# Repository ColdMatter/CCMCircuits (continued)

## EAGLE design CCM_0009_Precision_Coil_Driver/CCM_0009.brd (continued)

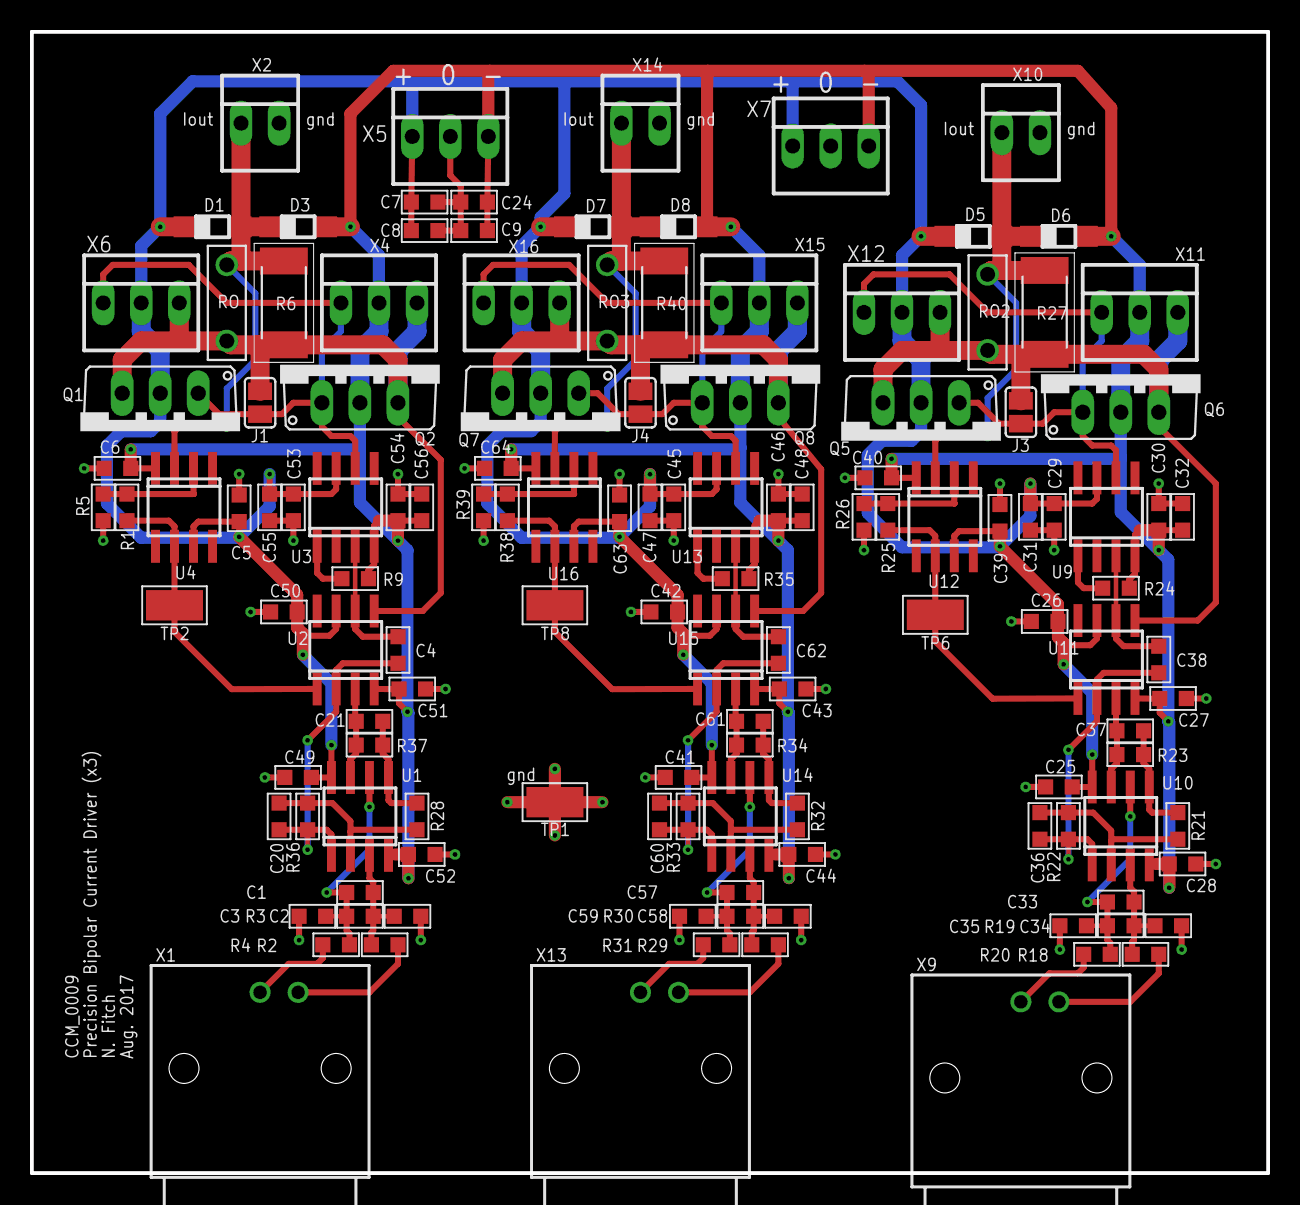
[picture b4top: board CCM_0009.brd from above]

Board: 2 copper layers, 82.5 x 76.2 mm, 130 parts (0 on the bottom side), 48 nets.

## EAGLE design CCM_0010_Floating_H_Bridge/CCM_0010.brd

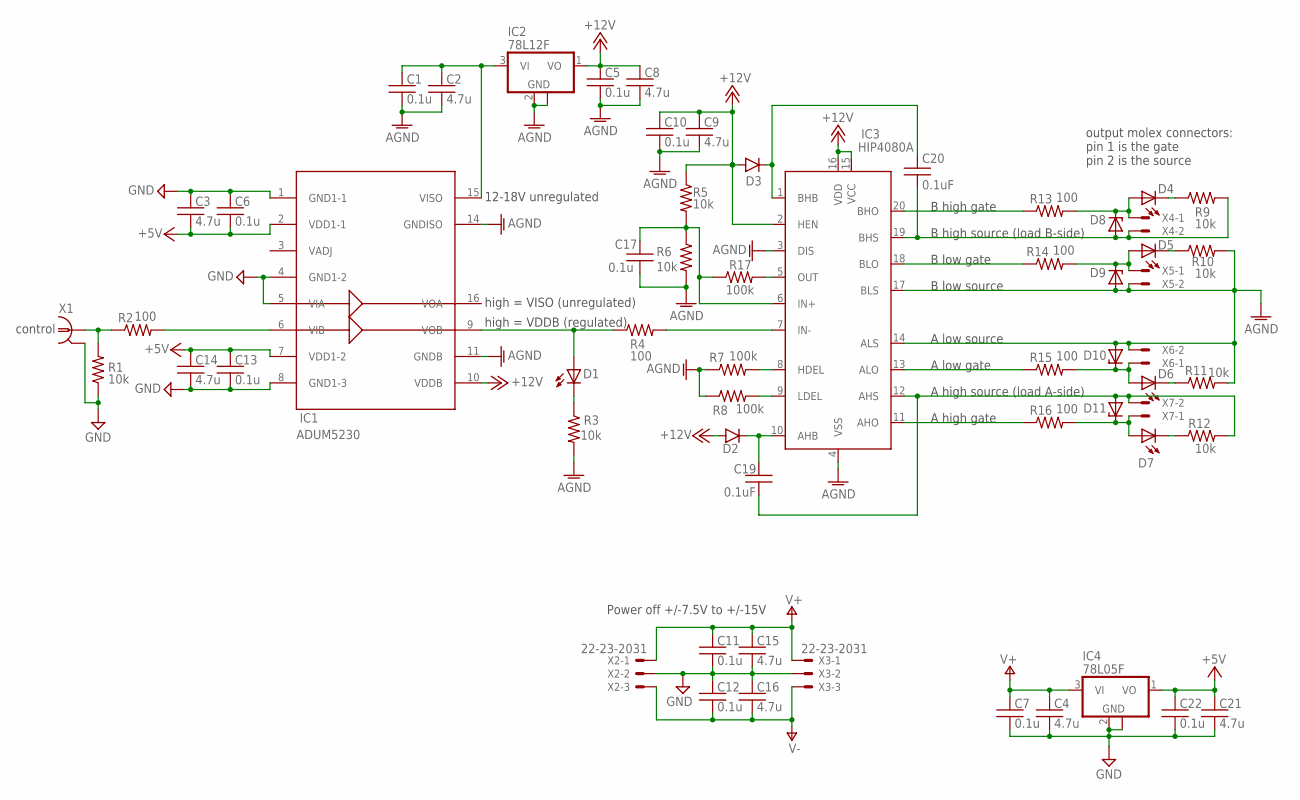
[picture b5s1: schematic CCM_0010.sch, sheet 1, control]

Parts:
C1, C5, C6, C7, C10, C11, C12, C13, C17, C22: 0.1u; 0603
C2, C3, C4, C8, C9, C14, C15, C16, C21: 4.7u; 0603
C19, C20: 0.1uF; 0603
D1, D4, D5, D6, D7: LED0603
D2, D3: DIODESOT23; SOT23-3
D8, D9, D10, D11: ZENER-DIODESOT23; SOT23
IC1: ADUM5230; SO16W
IC2: 78L12F; SOT89
IC3: HIP4080A; SO20W
IC4: 78L05F; SOT89
R1, R3, R5, R6, R9, R10, R11, R12: 10k; 0603
R2, R4, R13, R14, R15, R16: 100; 0603
R7, R8, R17: 100k; 0603
X1: 1-227161-0; AMP_227161
X2, X3: 22-23-2031
X4, X5, X6, X7: 22-23-2021

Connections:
+5V: C3.2, C6.2, C13.1, C14.1, C21.1, C22.1, IC1.2 (VDD1-1), IC1.7 (VDD1-2), IC4.1 (VO)
+12V: C5.1, C8.1, C9.1, C10.1, D2.1 (A), D3.1 (A), IC1.10 (VDDB), IC2.1 (VO), IC3.2 (HEN), IC3.15 (VCC), IC3.16 (VDD), R5.1
AGND: C1.2, C2.2, C5.2, C8.2, C9.2, C10.2, C17.2, D9.1 (A), D10.1 (A), IC1.11 (GNDB), IC1.14 (GNDISO), IC2.2 (GND), IC2.2@1 (GND), IC3.3 (DIS), IC3.4 (VSS), IC3.14 (ALS), IC3.17 (BLS), R3.2, R6.2, R7.1, R8.1, R10.2, R11.2, X5.2, X6.2
GND: C3.1, C4.2, C6.1, C7.2, C11.2, C12.1, C13.2, C14.2, C15.2, C16.1, C21.2, C22.2, IC1.1 (GND1-1), IC1.4 (GND1-2), IC1.5 (VIA), IC1.8 (GND1-3), IC4.2 (GND), IC4.2@1 (GND), R1.1, X1.2, X2.2, X3.2
unnamed: D1.C, R3.1
unnamed: D4.C, R9.1
unnamed: D5.C, R10.1
unnamed: IC3.20 (BHO), R13.1
unnamed: D5.A, D9.3 (C), R14.2, X5.1
unnamed: D6.C, R11.1
unnamed: D4.A, D8.3 (C), R13.2, X4.1
unnamed: D1.A, IC1.9 (VOB), R4.1
unnamed: D7.C, R12.1
unnamed: C1.1, C2.1, IC1.15 (VISO), IC2.3 (VI)
unnamed: IC3.11 (AHO), R16.1
unnamed: IC3.13 (ALO), R15.1
unnamed: IC3.7 (IN-), R4.2
unnamed: IC3.9 (LDEL), R8.2
unnamed: C20.2, D3.3 (C), IC3.1 (BHB)
unnamed: C20.1, D8.1 (A), IC3.19 (BHS), R9.2, X4.2
unnamed: IC3.18 (BLO), R14.1
unnamed: IC3.5 (OUT), R17.2
unnamed: C19.1, D11.1 (A), IC3.12 (AHS), R12.2, X7.2
unnamed: D7.A, D11.3 (C), R16.2, X7.1
unnamed: C19.2, D2.3 (C), IC3.10 (AHB)
unnamed: IC3.8 (HDEL), R7.2
unnamed: D6.A, D10.3 (C), R15.2, X6.1
unnamed: R1.2, R2.1, X1.1
unnamed: C17.1, IC3.6 (IN+), R5.2, R6.1, R17.1
unnamed: IC1.6 (VIB), R2.2
V+: C4.1, C7.1, C11.1, C15.1, IC4.3 (VI), X2.1, X3.1
V-: C12.2, C16.2, X2.3, X3.3

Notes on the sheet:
B high source (load B-side)
B high gate
B low gate
B low source
A high gate
A high source (load A-side)
A low gate
A low source
control
12-18V unregulated
high = VISO (unregulated)
high = VDDB (regulated)
Power off +/-7.5V to +/-15V
output molex connectors: pin 1 is the gate pin 2 is the source

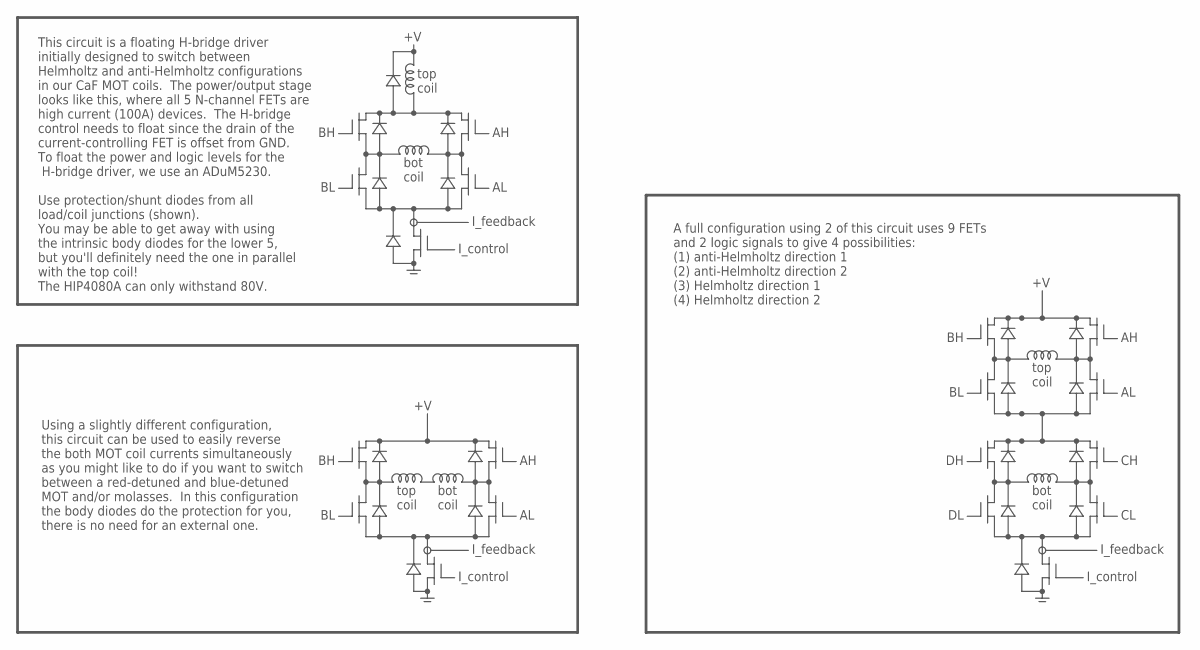
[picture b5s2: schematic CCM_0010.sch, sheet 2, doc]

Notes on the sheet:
I_control
top coil
bot coil
This circuit is a floating H-bridge driver initially designed to switch between Helmholtz and anti-Helmholtz configurations in our CaF MOT coils. The power/output stage looks like this, where all 5 N-channel FETs are high current (100A) devices. The H-bridge control needs to float since the drain o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
I_feedback
Using a slightly different configuration, this circuit can be used to easily reverse the both MOT coil currents simultaneously as you might like to do if you want to switch between a red-detuned and blue-detuned MOT and/or molasses. In this configuration the body diodes do the protection for you, t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
A full configuration using 2 of this circuit uses 9 FETs and 2 logic signals to give 4 possibilities: (1) anti-Helmholtz direction 1 (2) anti-Helmholtz direction 2 (3) Helmholtz direction 1 (4) Helmholtz direction 2

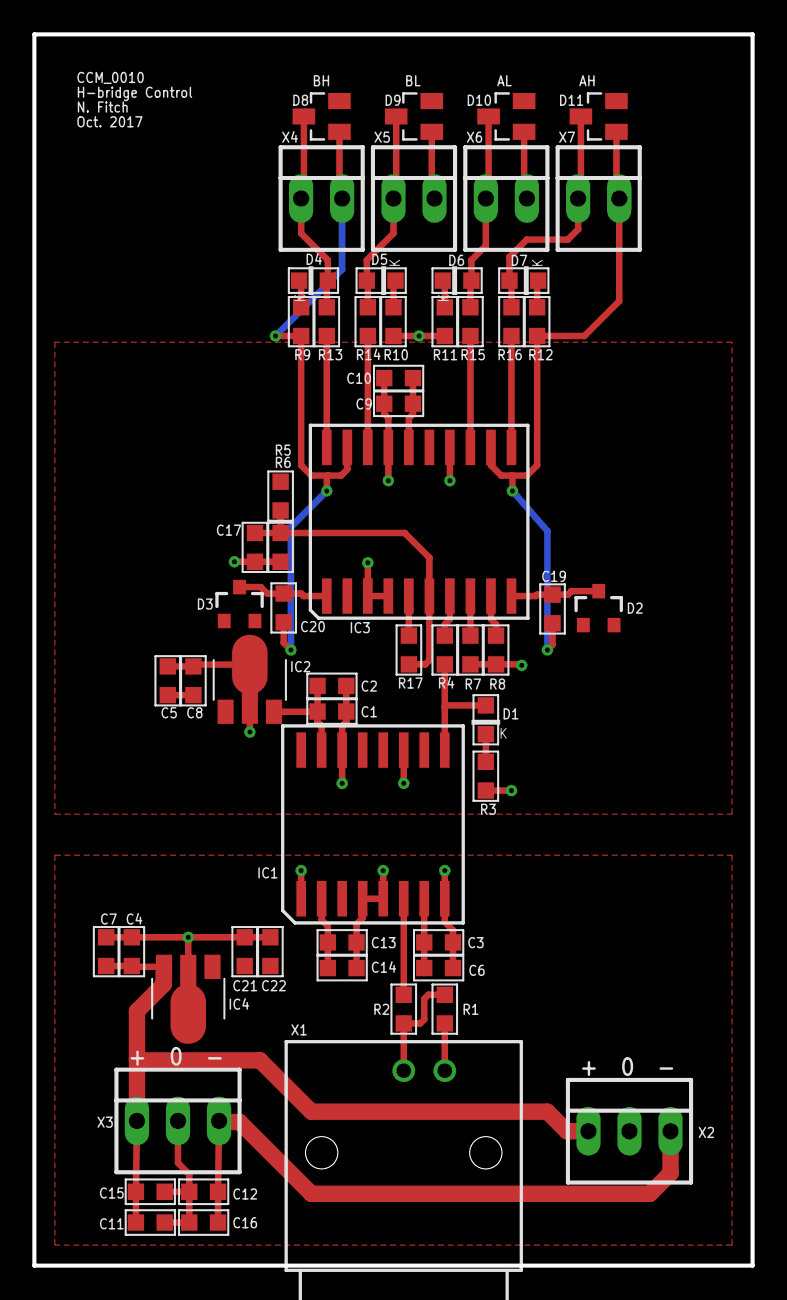
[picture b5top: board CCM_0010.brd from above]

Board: 2 copper layers, 44.5 x 76.2 mm, 60 parts (0 on the bottom side), 32 nets.
